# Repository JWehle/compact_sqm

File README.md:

# compact_sqm
A compact sky quality meter built on a custom PCB.

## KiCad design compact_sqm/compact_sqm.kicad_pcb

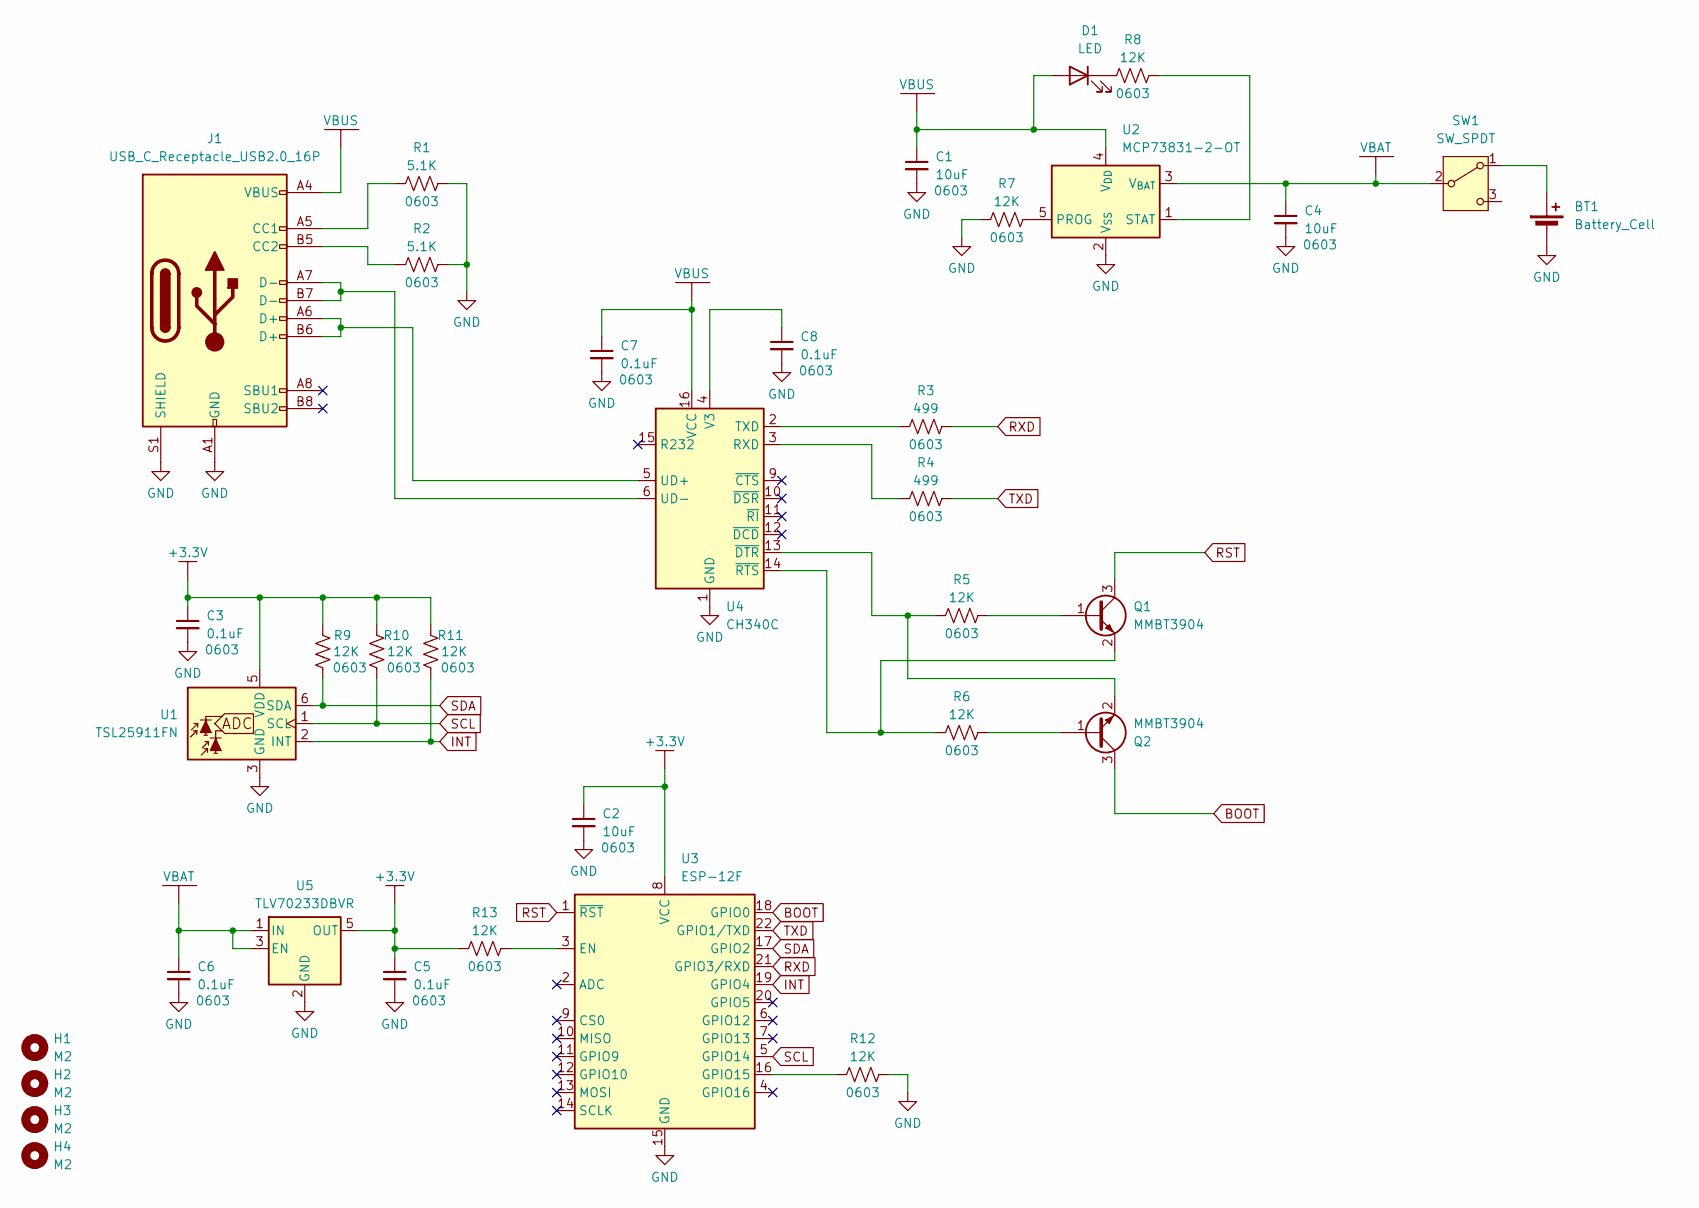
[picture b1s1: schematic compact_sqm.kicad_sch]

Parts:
BT1: Battery_Cell; PinHeader_2x01_P2.54mm_Vertical
C1, C2, C4: 10uF; C_0603_1608Metric
C3, C5, C6, C7, C8: 0.1uF; C_0603_1608Metric
D1: LED; LED_0603_1608Metric_Pad1.05x0.95mm_HandSolder
H1, H2, H3, H4: M2; MountingHole_2.2mm_M2
J1: USB_C_Receptacle_USB2.0_16P; USB_C_Receptacle_GCT_USB4110
Q1, Q2: MMBT3904; SOT-23
R1, R2: 5.1K; R_0603_1608Metric
R3, R4: 499; R_0603_1608Metric
R5, R6, R7, R8, R9, R10, R11, R12, R13: 12K; R_0603_1608Metric
SW1: SW_SPDT; SW_SPDT_PCM12
U1: TSL25911FN; AMS_TSL25911FN
U2: MCP73831-2-OT; SOT-23-5
U3: ESP-12F; ESP-12E
U4: CH340C; SOIC-16_3.9x9.9mm_P1.27mm
U5: TLV70233DBVR; SOT-23-5

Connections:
+3.3V: C2.1, C3.1, C5.1, R9.2, R10.2, R11.2, R13.1, U1.5 (VDD), U3.8 (VCC), U5.5 (OUT)
BOOT: Q2.3 (C), U3.18 (GPIO0)
GND: BT1.2 (-), C1.2, C2.2, C3.2, C4.2, C5.2, C6.2, C7.2, C8.2, J1.A1 (GND), J1.A12 (GND), J1.B1 (GND), J1.B12 (GND), J1.S1 (SHIELD), R1.2, R2.2, R7.1, R12.2, U1.3 (GND), U2.2 (V_{SS}), U3.15 (GND), U4.1 (GND), U5.2 (GND)
INT: R11.1, U1.2 (INT), U3.19 (GPIO4)
unnamed: BT1.1 (+), SW1.1 (A)
unnamed: D1.1 (K), R8.1
unnamed: J1.A5 (CC1), R1.1
unnamed: J1.B5 (CC2), R2.1
unnamed: Q1.1 (B), R5.2
unnamed: Q1.2 (E), R6.1, U4.14 (~RTS)
unnamed: Q2.1 (B), R6.2
unnamed: Q2.2 (E), R5.1, U4.13 (~DTR)
unnamed: R7.2, U2.5 (PROG)
unnamed: R8.2, U2.1 (STAT)
unnamed: R13.2, U3.3 (EN)
unnamed: R12.1, U3.16 (GPIO15)
unnamed: R4.1, U4.3 (RXD)
unnamed: R3.1, U4.2 (TXD)
unnamed: J1.A6 (D+), J1.B6 (D+), U4.5 (UD+)
unnamed: J1.A7 (D-), J1.B7 (D-), U4.6 (UD-)
unnamed: C8.1, U4.4 (V3)
RST: Q1.3 (C), U3.1 (~RST)
RXD: R3.2, U3.21 (GPIO3/RXD)
SCL: R10.1, U1.1 (SCL), U3.5 (GPIO14)
SDA: R9.1, U1.6 (SDA), U3.17 (GPIO2)
TXD: R4.2, U3.22 (GPIO1/TXD)
VBAT: C4.1, C6.1, SW1.2 (B), U2.3 (V_{BAT}), U5.1 (IN), U5.3 (EN)
VBUS: C1.1, C7.1, D1.2 (A), J1.A4 (VBUS), J1.A9 (VBUS), J1.B4 (VBUS), J1.B9 (VBUS), U2.4 (V_{DD}), U4.16 (VCC)

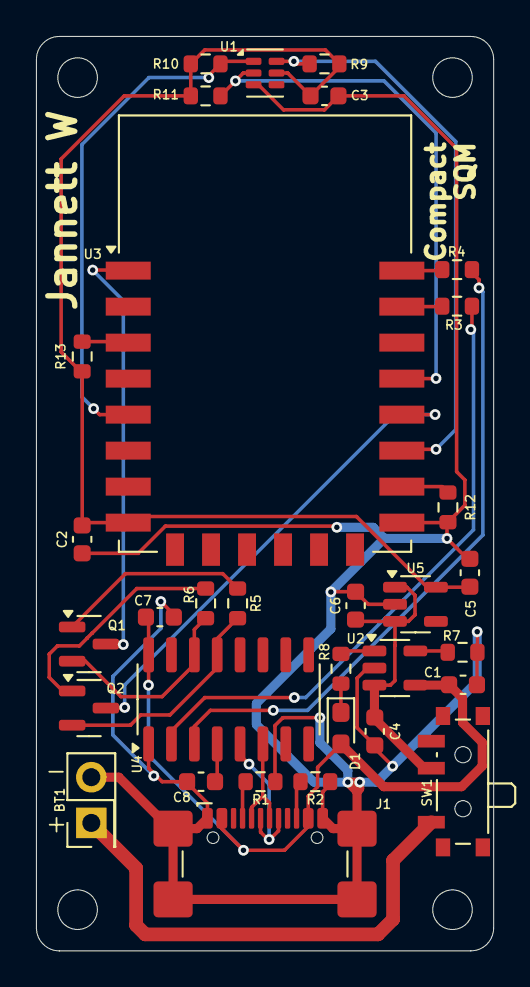
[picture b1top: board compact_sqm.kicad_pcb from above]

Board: 2 copper layers, 25.4 x 50.8 mm, 36 parts (0 on the bottom side), 28 nets.

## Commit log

2025-01-20 schematic edits
2025-01-21 finished schematic
2025-01-21 layout updates
2025-01-21 finished layout
2025-01-24 gerbers
2025-01-31 parts list
2025-01-31 schematic
